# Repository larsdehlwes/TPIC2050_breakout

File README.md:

# TPIC2050_breakout
Provisory breakout board for the [TPIC2050](https://www.ti.com/product/TPIC2050), a 3-beam laser diode driver and 9-channel motor driver, for DVD and Blu-Ray drives. The circuit follows too good part the Typical Application circuit from [Section 9.2](https://www.ti.com/document-viewer/TPIC2050/datasheet/application_and_implementation#SLIS1675680) of the Datasheet, with the exception that P5V12L (the power-supply for the load driver) is hard-connected to P5V (the power-supply for the 5V driver such as tilt/track/focus).

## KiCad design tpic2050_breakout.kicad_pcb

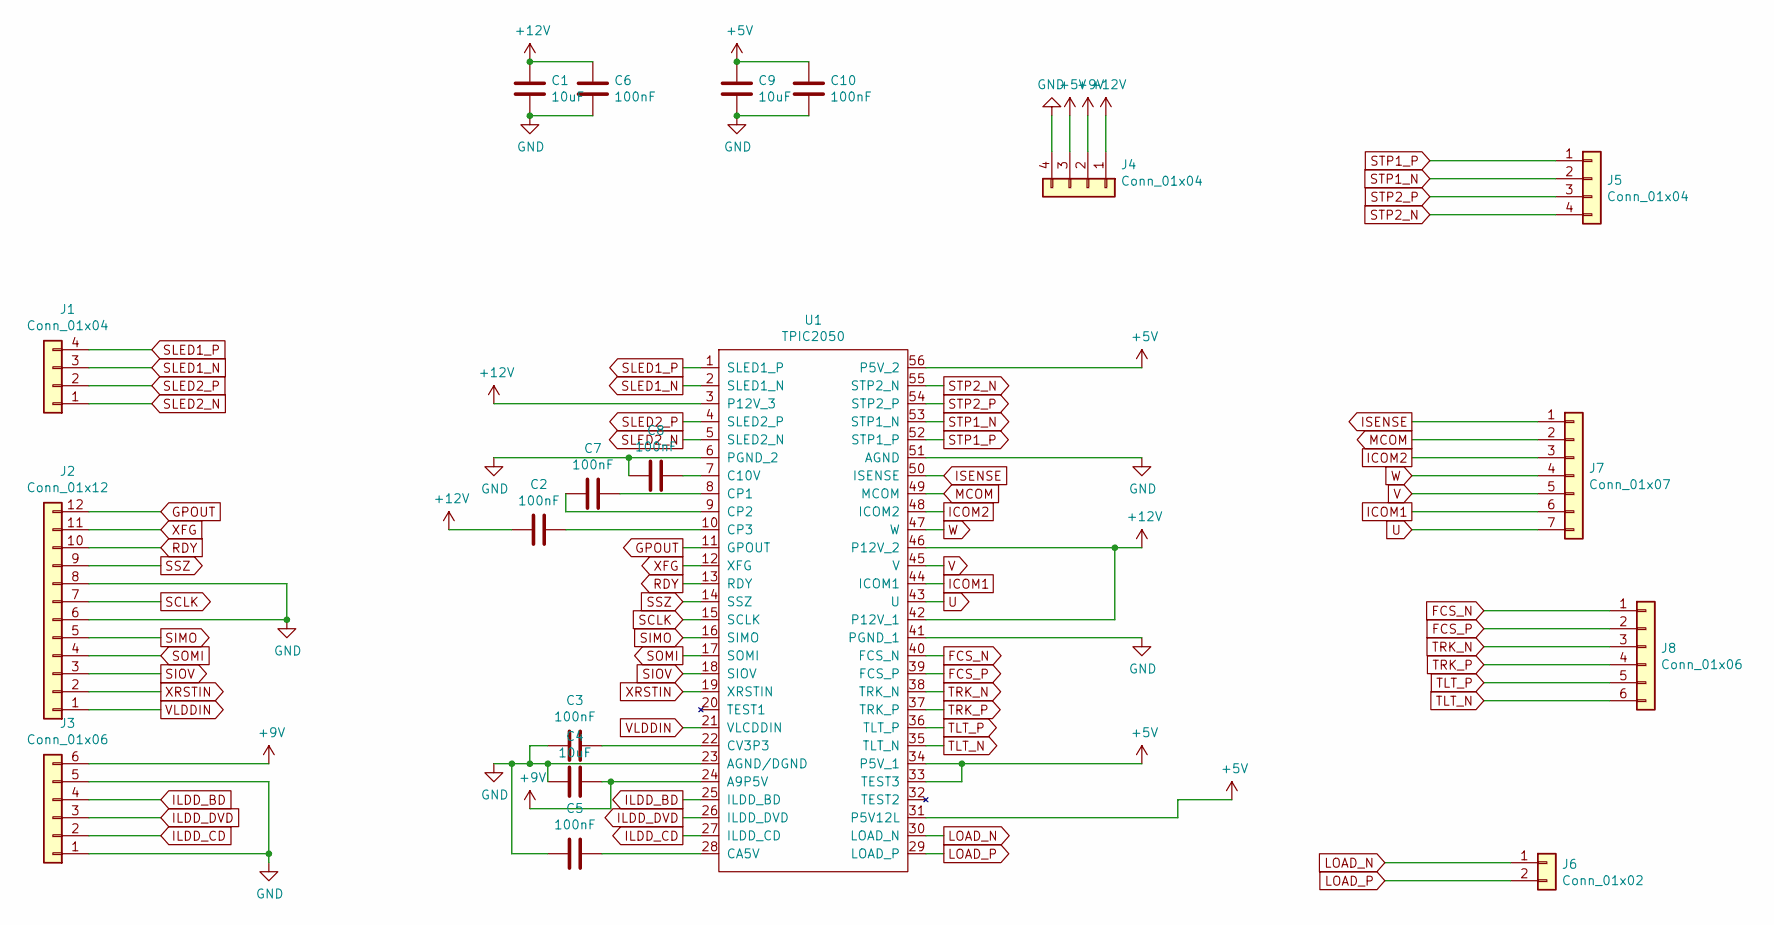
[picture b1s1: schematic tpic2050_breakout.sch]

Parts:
C1, C4, C9: 10uF; C_0805_2012Metric
C2, C3, C5, C6, C7, C8, C10: 100nF; C_0402_1005Metric
J1, J4, J5: Conn_01x04; PinHeader_1x04_P2.54mm_Vertical
J2: Conn_01x12; PinHeader_1x12_P2.54mm_Vertical
J3, J8: Conn_01x06; PinHeader_1x06_P2.54mm_Vertical
J6: Conn_01x02; PinHeader_1x02_P2.54mm_Vertical
J7: Conn_01x07; PinHeader_1x07_P2.54mm_Vertical
U1: TPIC2050; TSSOP-56_6.1x14mm_P0.5mm

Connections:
+5V: C9.1, C10.1, J4.3, U1.31 (P5V12L), U1.33 (TEST3), U1.34 (P5V_1), U1.56 (P5V_2)
+9V: C4.1, J3.6, J4.2, U1.24 (A9P5V)
+12V: C1.1, C2.2, C6.1, J4.1, U1.3 (P12V_3), U1.42 (P12V_1), U1.46 (P12V_2)
FCS_N: J8.1, U1.40 (FCS_N)
FCS_P: J8.2, U1.39 (FCS_P)
GND: C1.2, C3.2, C4.2, C5.2, C6.2, C8.2, C9.2, C10.2, J2.6, J2.8, J3.1, J3.5, J4.4, U1.6 (PGND_2), U1.23 (AGND/DGND), U1.41 (PGND_1), U1.51 (AGND)
GPOUT: J2.12, U1.11 (GPOUT)
ICOM1: J7.6, U1.44 (ICOM1)
ICOM2: J7.3, U1.48 (ICOM2)
ILDD_BD: J3.4, U1.25 (ILDD_BD)
ILDD_CD: J3.2, U1.27 (ILDD_CD)
ILDD_DVD: J3.3, U1.26 (ILDD_DVD)
ISENSE: J7.1, U1.50 (ISENSE)
LOAD_N: J6.1, U1.30 (LOAD_N)
LOAD_P: J6.2, U1.29 (LOAD_P)
MCOM: J7.2, U1.49 (MCOM)
unnamed: C2.1, U1.10 (CP3)
unnamed: C3.1, U1.22 (CV3P3)
unnamed: C5.1, U1.28 (CA5V)
unnamed: C7.1, U1.8 (CP1)
unnamed: C7.2, U1.9 (CP2)
unnamed: C8.1, U1.7 (C10V)
RDY: J2.10, U1.13 (RDY)
SCLK: J2.7, U1.15 (SCLK)
SIMO: J2.5, U1.16 (SIMO)
SIOV: J2.3, U1.18 (SIOV)
SLED1_N: J1.3, U1.2 (SLED1_N)
SLED1_P: J1.4, U1.1 (SLED1_P)
SLED2_N: J1.1, U1.5 (SLED2_N)
SLED2_P: J1.2, U1.4 (SLED2_P)
SOMI: J2.4, U1.17 (SOMI)
SSZ: J2.9, U1.14 (SSZ)
STP1_N: J5.2, U1.53 (STP1_N)
STP1_P: J5.1, U1.52 (STP1_P)
STP2_N: J5.4, U1.55 (STP2_N)
STP2_P: J5.3, U1.54 (STP2_P)
TLT_N: J8.6, U1.35 (TLT_N)
TLT_P: J8.5, U1.36 (TLT_P)
TRK_N: J8.3, U1.38 (TRK_N)
TRK_P: J8.4, U1.37 (TRK_P)
U: J7.7, U1.43 (U)
V: J7.5, U1.45 (V)
VLDDIN: J2.1, U1.21 (VLCDDIN)
W: J7.4, U1.47 (W)
XFG: J2.11, U1.12 (XFG)
XRSTIN: J2.2, U1.19 (XRSTIN)

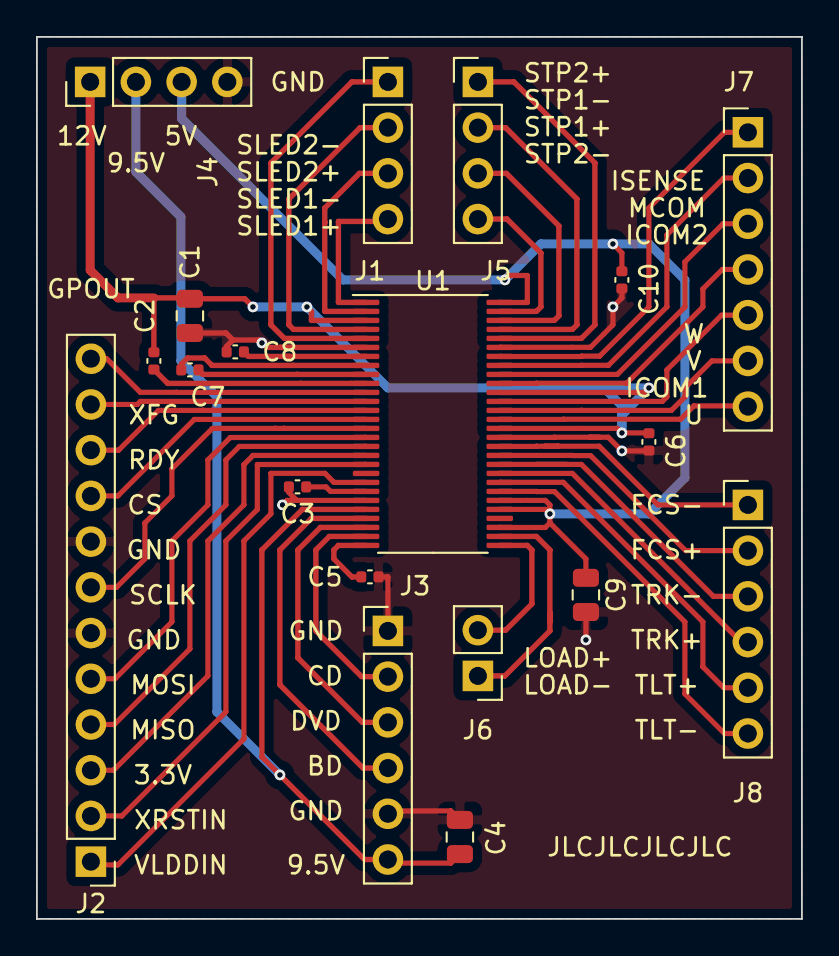
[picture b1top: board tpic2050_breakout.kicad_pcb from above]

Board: 2 copper layers, 42.5 x 49.0 mm, 19 parts (0 on the bottom side), 46 nets.

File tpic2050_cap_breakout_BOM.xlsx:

Comment | Designator | Footprint | JLCPCB Part #（optional）
10uF | C1,C4,C9 | C_0805_2012Metric | C15850
100nF | C2,C3,C5,C6,C7,C8,C10 | C_0402_1005Metric | C1525

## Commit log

2021-09-05 Added first version of the breakout board
2021-09-05 updated .gitignore
